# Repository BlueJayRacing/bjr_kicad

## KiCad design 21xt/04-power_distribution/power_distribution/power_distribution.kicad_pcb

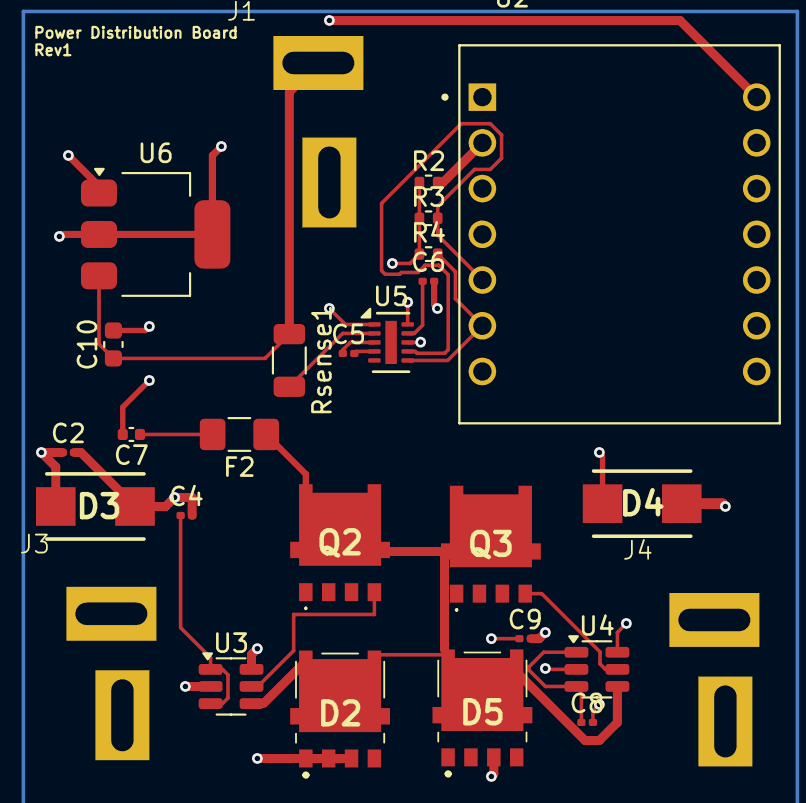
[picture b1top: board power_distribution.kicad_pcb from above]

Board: 4 copper layers, 27 parts (0 on the bottom side), 19 nets.

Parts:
C2, C4, C8, C9: 10 uF; C_0201_0603Metric
C5: 470 nF; C_0201_0603Metric
C6: 1 uF; C_0201_0603Metric
C7: 10uF; C_0402_1005Metric
C10: 100uF; C_0603_1608Metric
D2, D5: NRVB10100MFST1G; NRVTS10100EMFST1G
D3, D4: SMBJ33CA
F2: Fuse; Fuse_1206_3216Metric_Pad1.42x1.75mm_HandSolder
J1: Conn_01x02; Deans Connector Female
J3, J4: Conn_01x02; Deans Connector Male
Q2, Q3: NVMFWS2D1N08XT1G; NTMFWS1D5N08XT1G
R2, R3, R4: 2k; R_0402_1005Metric
Rsense1: 50 mOhms; R_1206_3216Metric
U2: XIAO-ESP32-C3-DIP; esp32 c6 xiao
U3, U4: LM74700; SOT-23-6
U5: LTC2959; DFN-10-1EP_2x3mm_P0.5mm_EP0.64x2.4mm
U6: TLV76150DCY; SOT-223-3_TabPin2

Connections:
3V3 ESP32: R2.1, R3.1, R4.1, U2.12 (VCC_3V3), U5.8 (GPIO)
5 LinReg: U2.14 (VBUS), U5.1 (V_{DD}), U6.2 (VO)
Battery1: C8.2, C9.2, D4.2, D5.1 (S_1), D5.2 (S_2), D5.3 (S_3), J4.1, U4.6 (ANODE)
Battery1_Supply: D2.5 (D_1), D2.6 (D_2), D2.7 (D_3), D2.8 (D_4), D2.9 (D_5), D5.5 (D_1), D5.6 (D_2), D5.7 (D_3), D5.8 (D_4), D5.9 (D_5), F2.1, Q2.5 (D_1), Q2.6 (D_2), Q2.7 (D_3), Q2.8 (D_4), Q2.9 (D_5), Q3.5 (D_1), Q3.6 (D_2), Q3.7 (D_3), Q3.8 (D_4), Q3.9 (D_5), U3.4 (CATHODE), U4.4 (CATHODE)
Battery2: C2.2, C4.2, D2.1 (S_1), D2.2 (S_2), D2.3 (S_3), D3.2, J3.1, U3.6 (ANODE)
GND: C2.1, C6.2, C7.2, C9.1, C10.2, D3.1, D4.1, J1.2, J3.2, J4.2, U2.13 (GND), U3.2 (GND), U4.2 (GND), U5.10 (GND), U6.1 (GND)
unnamed: C7.1, F2.2
unnamed: C10.1, J1.1, Rsense1.1, U6.3 (VI)
unnamed: Q2.4 (G), U3.5 (GATE)
unnamed: Q3.4 (G), U4.5 (GATE)
unnamed: R2.2, U2.2 (GPIO3/A1/D1)
unnamed: C4.1, U3.1 (VCAP), U3.3 (EN)
unnamed: C8.1, U4.1 (VCAP), U4.3 (EN)
unnamed: C5.2, U5.4 (CFN)
unnamed: C5.1, U5.3 (CFP)
unnamed: Rsense1.2, U5.2 (SENSEP)
unnamed: C6.1, U5.9 (V_{REG})
SCL: R4.2, U2.6 (GPIO7/D5/SCL), U5.6 (SCL)
SDA: R3.2, U2.5 (GPIO6/D4/SDA), U5.7 (SDA)

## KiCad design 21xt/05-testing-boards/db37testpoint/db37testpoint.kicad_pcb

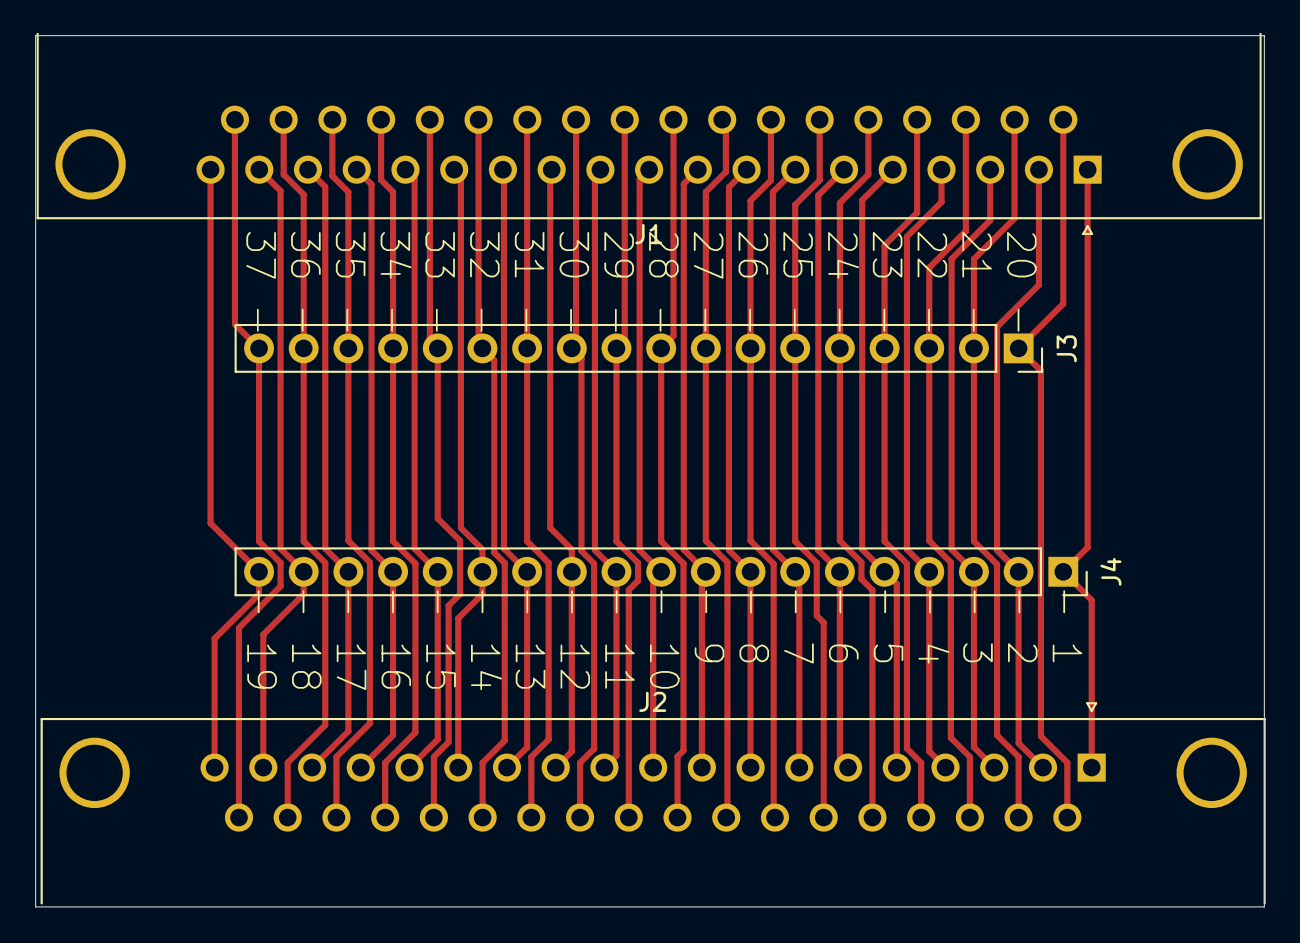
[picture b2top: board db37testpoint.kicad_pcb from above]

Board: 2 copper layers, 69.8 x 49.5 mm, 4 parts (0 on the bottom side), 37 nets.

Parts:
J1: DC37_Plug; DSUB-37_Male_Horizontal_P2.77x2.84mm_EdgePinOffset4.94mm_Ho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
J2: DC37_Receptacle; DSUB-37_Female_Horizontal_P2.77x2.84mm_EdgePinOffset4.94mm_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
J3: Conn_01x18_Pin; PinSocket_1x18_P2.54mm_Vertical
J4: Conn_01x19_Pin; PinSocket_1x19_P2.54mm_Vertical

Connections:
1: J1.1, J2.1, J4.1
2: J1.2, J2.2, J4.2
3: J1.3, J2.3, J4.3
4: J1.4, J2.4, J4.4
5: J1.5, J2.5, J4.5
6: J1.6, J2.6, J4.6
7: J1.7, J2.7, J4.7
8: J1.8, J2.8, J4.8
9: J1.9, J2.9, J4.9
10: J1.10, J2.10, J4.10
11: J1.11, J2.11, J4.11
12: J1.12, J2.12, J4.12
13: J1.13, J2.13, J4.13
14: J1.14, J2.14, J4.14
15: J1.15, J2.15, J4.15
16: J1.16, J2.16, J4.16
17: J1.17, J2.17, J4.17
18: J1.18, J2.18, J4.18
19: J1.19, J2.19, J4.19
20: J1.20, J2.20, J3.1
21: J1.21, J2.21, J3.2
22: J1.22, J2.22, J3.3
23: J1.23, J2.23, J3.4
24: J1.24, J2.24, J3.5
25: J1.25, J2.25, J3.6
26: J1.26, J2.26, J3.7
27: J1.27, J2.27, J3.8
28: J1.28, J2.28, J3.9
29: J1.29, J2.29, J3.10
30: J1.30, J2.30, J3.11
31: J1.31, J2.31, J3.12
32: J1.32, J2.32, J3.13
33: J1.33, J2.33, J3.14
34: J1.34, J2.34, J3.15
35: J1.35, J2.35, J3.16
36: J1.36, J2.36, J3.17
37: J1.37, J2.37, J3.18

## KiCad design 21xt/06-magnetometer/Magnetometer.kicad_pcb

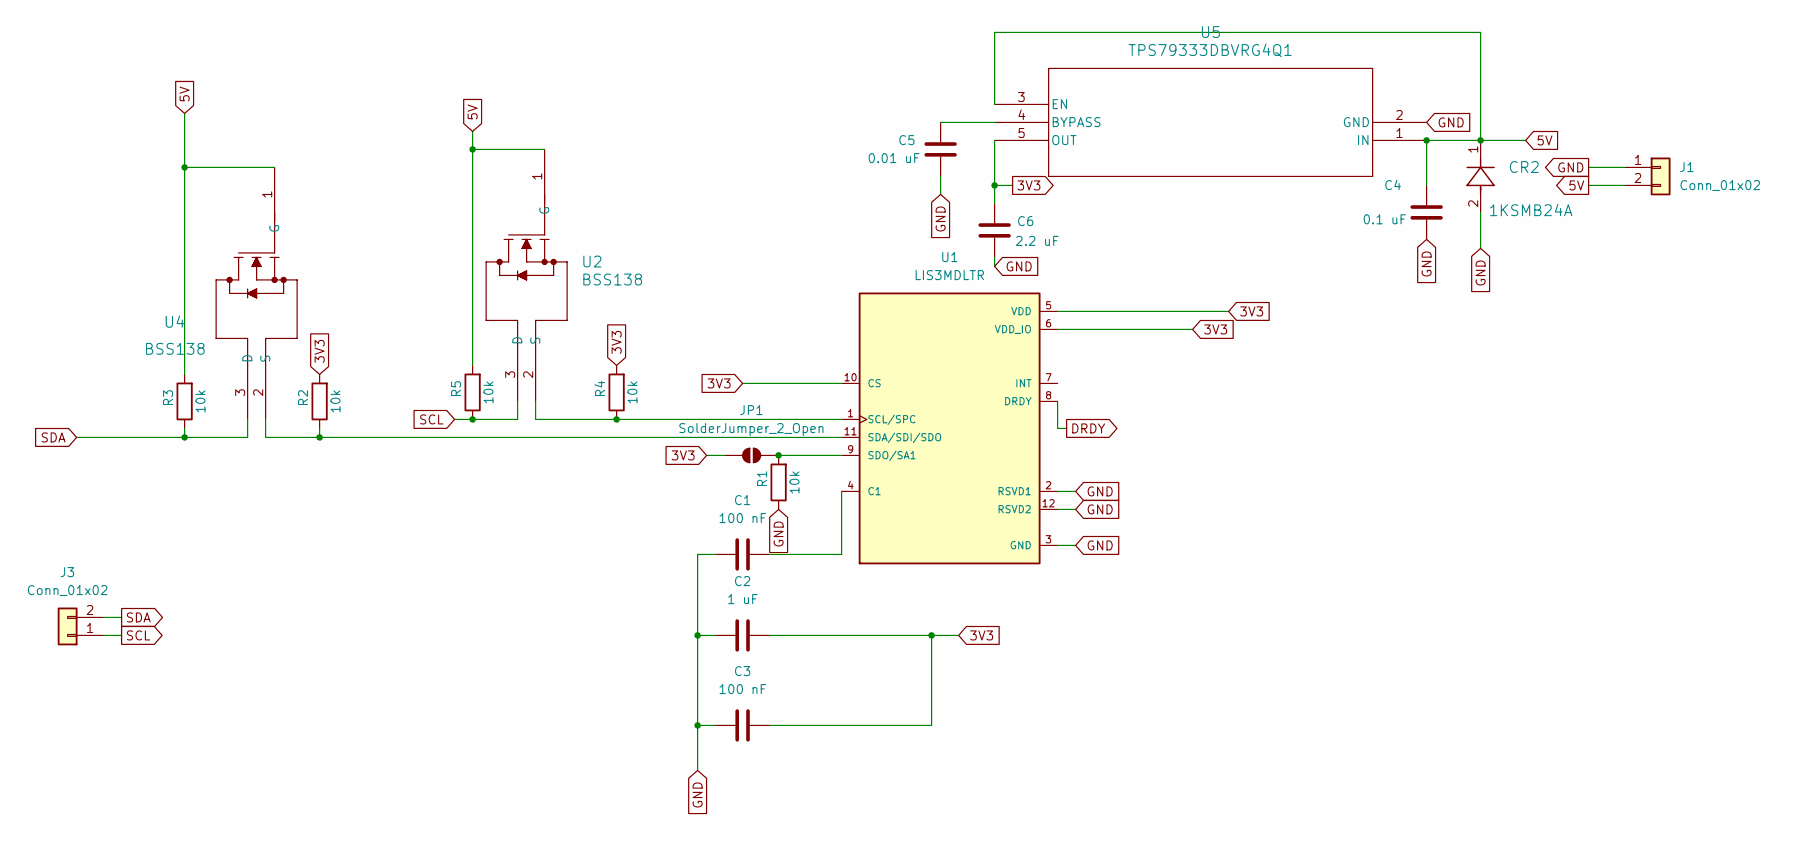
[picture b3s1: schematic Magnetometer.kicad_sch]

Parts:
C1, C3: 100 nF; C_0402_1005Metric
C2: 1 uF; C_0402_1005Metric
C4: 0.1 uF; C_0402_1005Metric
C5: 0.01 uF; C_0402_1005Metric
C6: 2.2 uF; C_0402_1005Metric
CR2: 1KSMB24A; 1KSMBSeries_LTF
J1, J3: Conn_01x02; Connector
JP1: SolderJumper_2_Open; SolderJumper
R1, R2, R3, R4, R5: 10k; R_0402_1005Metric
U1: LIS3MDLTR; PARTREV 6
U2, U4: BSS138
U5: TPS79333DBVRG4Q1; DBV5_TEX

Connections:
3V3: C2.2, C3.2, C6.1, JP1.1 (A), R2.2, R4.2, U1.5 (VDD), U1.6 (VDD_IO), U1.10 (CS), U5.5 (OUT)
5V: C4.1, CR2.1, J1.2, R3.2, R5.2, U2.1 (G), U4.1 (G), U5.1 (IN), U5.3 (EN)
DRDY: U1.8 (DRDY)
GND: C1.1, C2.1, C3.1, C4.2, C5.2, C6.2, CR2.2, J1.1, R1.1, U1.2 (RSVD1), U1.3 (GND), U1.12 (RSVD2), U5.2 (GND)
unnamed: JP1.2 (B), R1.2, U1.9 (SDO/SA1)
unnamed: C1.2, U1.4 (C1)
unnamed: R4.1, U1.1 (SCL/SPC), U2.2 (S)
unnamed: R2.1, U1.11 (SDA/SDI/SDO), U4.2 (S)
unnamed: C5.1, U5.4 (BYPASS)
SCL: J3.1, R5.1, U2.3 (D)
SDA: J3.2, R3.1, U4.3 (D)

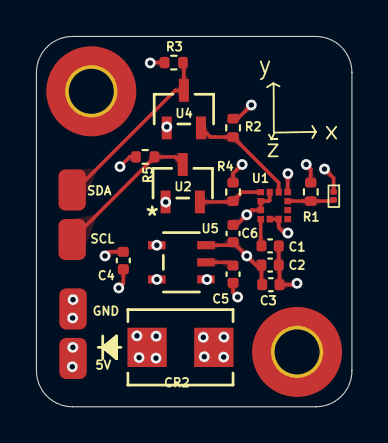
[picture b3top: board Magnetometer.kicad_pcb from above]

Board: 4 copper layers, 17.5 x 20.6 mm, 19 parts (0 on the bottom side), 10 nets.

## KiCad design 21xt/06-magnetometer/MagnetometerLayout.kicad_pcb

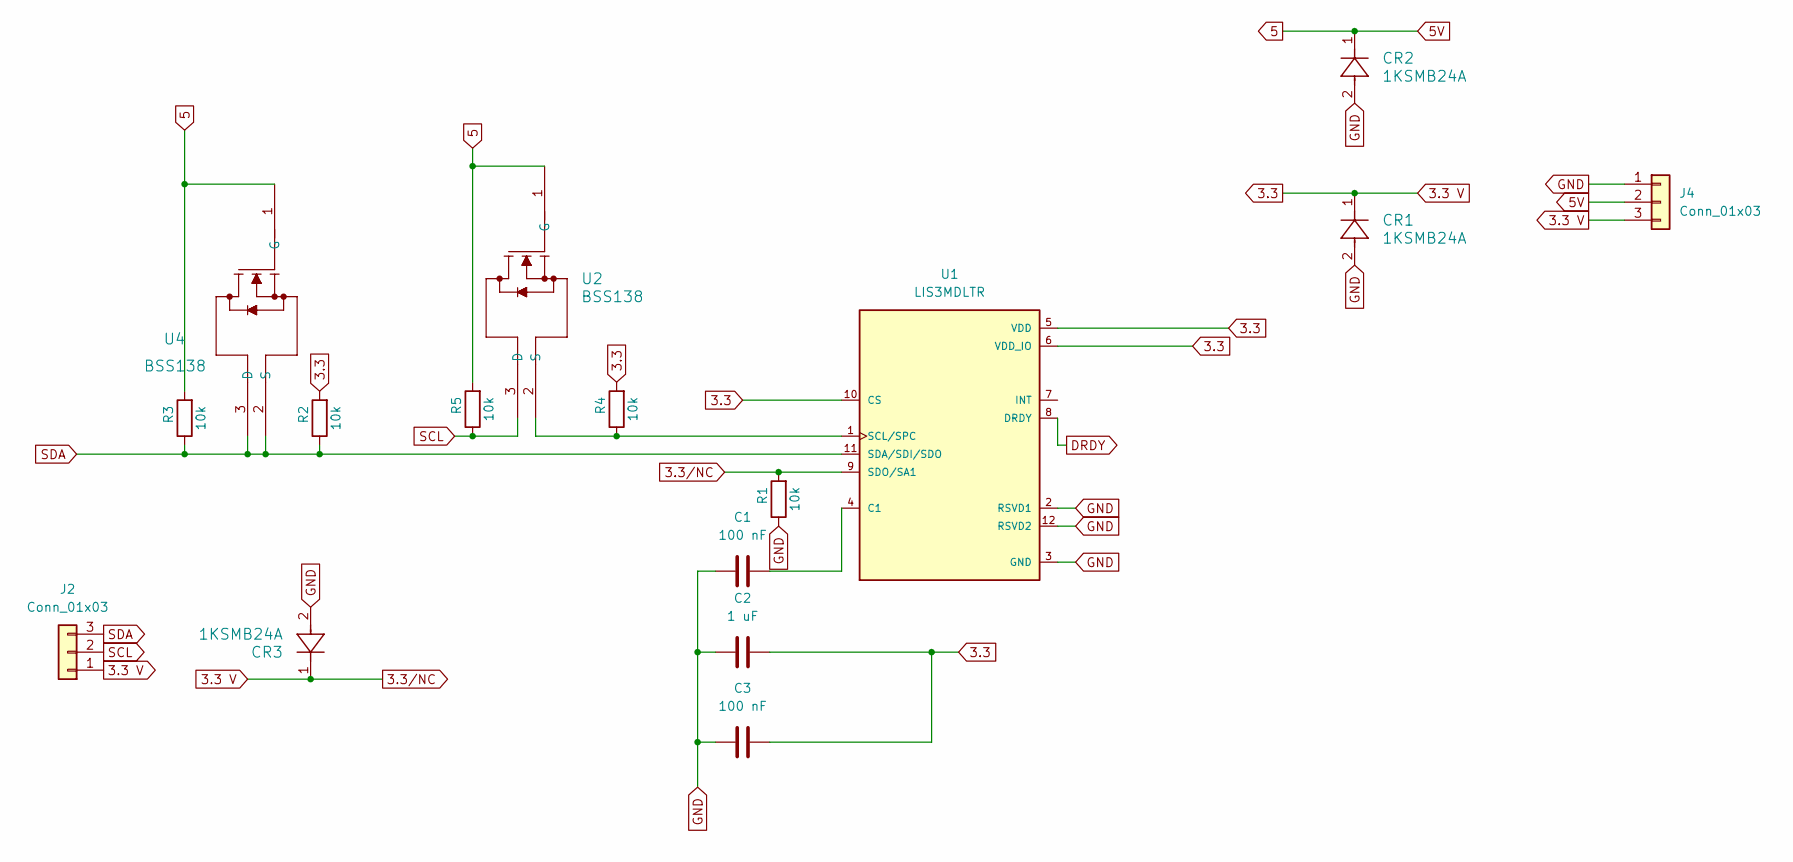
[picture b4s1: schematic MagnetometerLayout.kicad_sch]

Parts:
C1, C3: 100 nF; CP_Elec_3x5.3
C2: 1 uF; CP_Elec_3x5.3
CR1, CR2, CR3: 1KSMB24A
J2, J4: Conn_01x03; JST_EH_B3B-EH-A_1x03_P2.50mm_Vertical
R1, R2, R3, R4, R5: 10k; R_0201_0603Metric_Pad0.64x0.40mm_HandSolder
U1: LIS3MDLTR; XDCR_LIS3MDLTR; PARTREV 6
U2, U4: BSS138

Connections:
3.3: C2.2, C3.2, CR1.1, CR3.1, J2.1, J4.3, R1.2, R2.2, R4.2, U1.5 (VDD), U1.6 (VDD_IO), U1.9 (SDO/SA1), U1.10 (CS)
5: CR2.1, J4.2, R3.2, R5.2, U2.1 (G), U4.1 (G)
DRDY: U1.8 (DRDY)
GND: C1.1, C2.1, C3.1, CR1.2, CR2.2, CR3.2, J4.1, R1.1, U1.2 (RSVD1), U1.3 (GND), U1.12 (RSVD2)
unnamed: C1.2, U1.4 (C1)
unnamed: R4.1, U1.1 (SCL/SPC), U2.2 (S)
SCL: J2.2, R5.1, U2.3 (D)
SDA: J2.3, R2.1, R3.1, U1.11 (SDA/SDI/SDO), U4.2 (S), U4.3 (D)

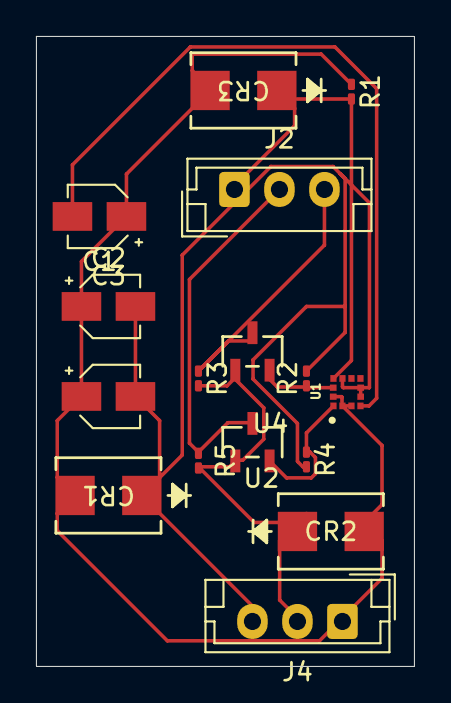
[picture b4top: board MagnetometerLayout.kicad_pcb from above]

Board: 2 copper layers, 21.0 x 35.0 mm, 16 parts (0 on the bottom side), 7 nets.

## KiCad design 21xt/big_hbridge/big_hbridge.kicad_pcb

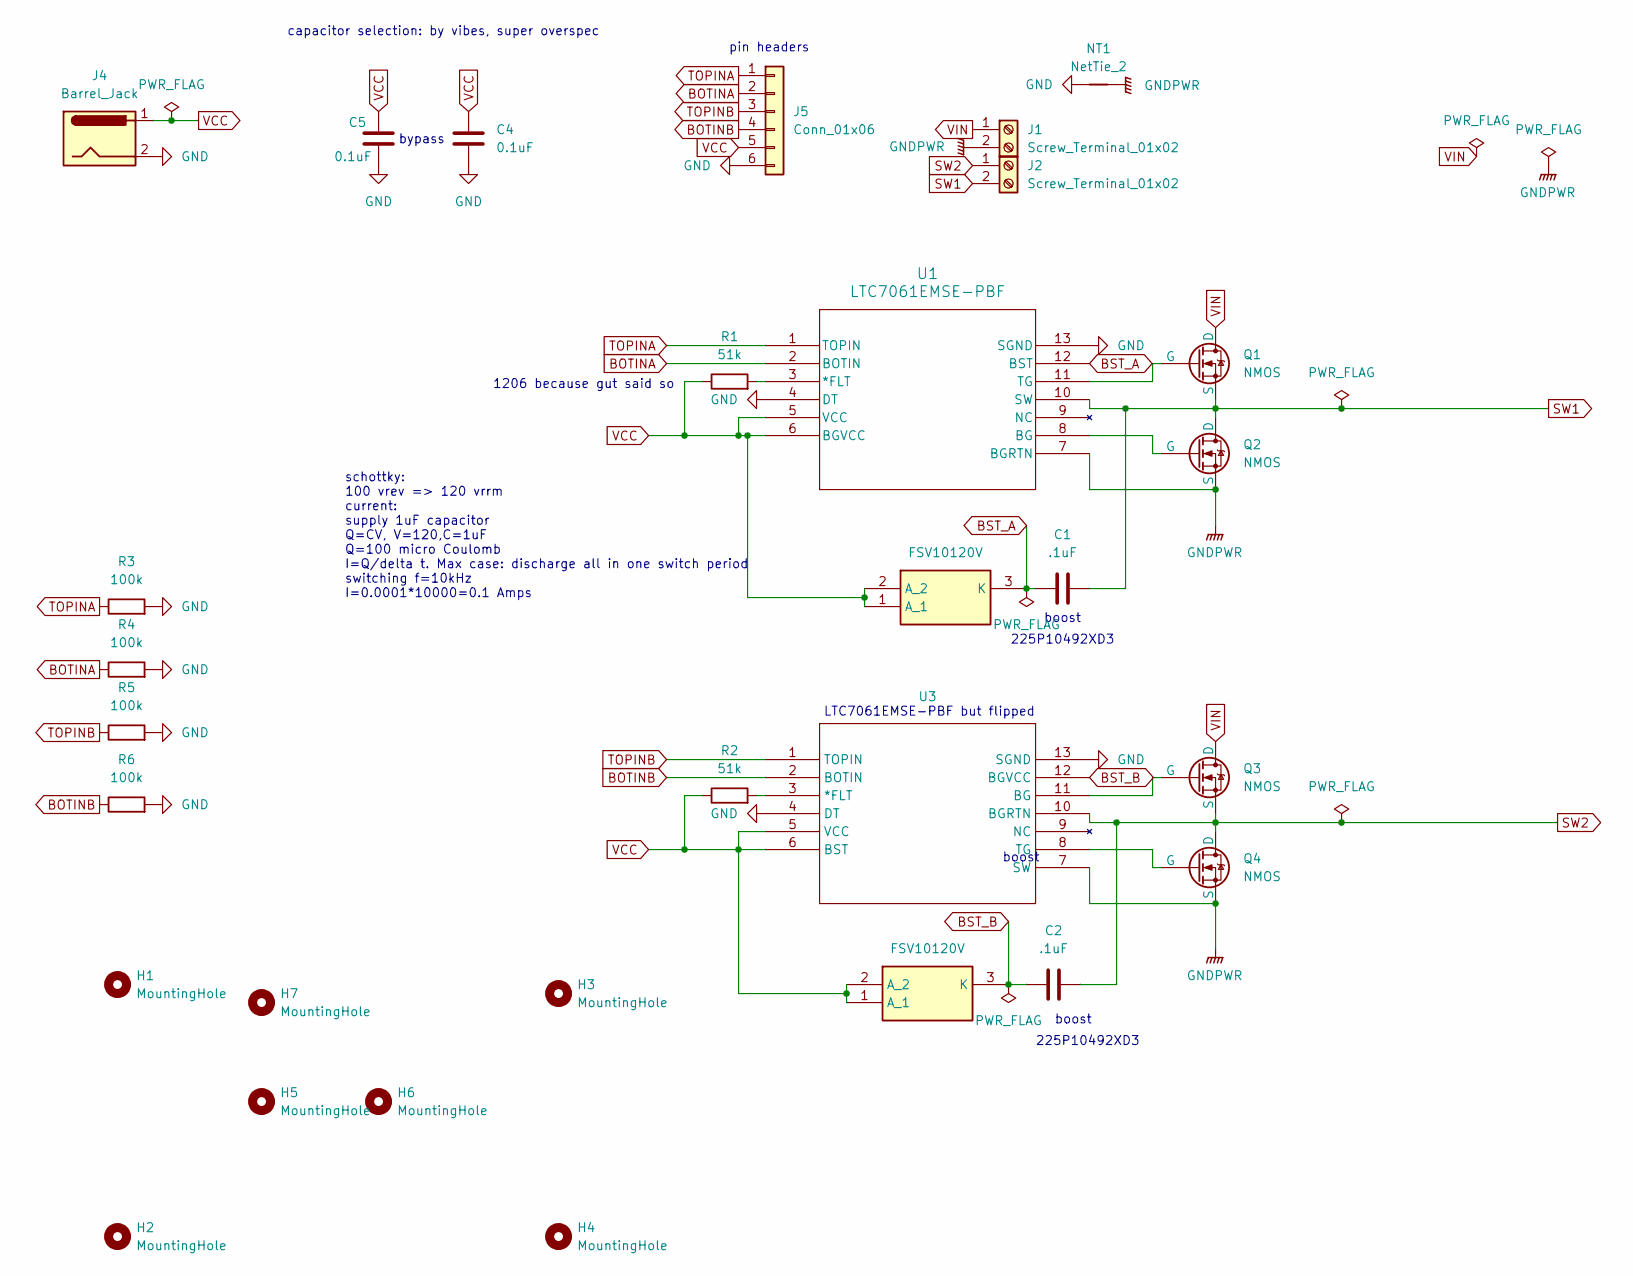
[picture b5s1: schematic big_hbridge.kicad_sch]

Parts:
C1, C2: .1uF; C_Disc_D7.5mm_W5.0mm_P10.00mm
C4, C5: 0.1uF; C_1206_3216Metric
D1, D3: FSV10120V; Mouser Part Number 512-FSV10120V
H1, H2, H3, H4, H5, H6, H7: MountingHole; MountingHole_3mm_Pad
J1, J2: Screw_Terminal_01x02; CONN_4DB-P108-02_TEC
J4: Barrel_Jack; BarrelJack_Horizontal
J5: Conn_01x06; PinHeader_1x06_P2.54mm_Vertical
NT1: NetTie_2; NetTie-2_THT_Pad1.0mm
Q1, Q2, Q3, Q4: NMOS; TO254P1524X483-3N
R1, R2: 51k; R_1206_3216Metric
R3, R4, R5: 100k; R_0402_1005Metric
R6: 100k; LED_0402_1005Metric
U1: LTC7061EMSE-PBF; MSOP12_MSE_ADI-M
U3: MSOP12_MSE_ADI-M

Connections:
BOTINA: J5.2, R4.1, U1.2 (BOTIN)
BOTINB: J5.4, R6.1, U3.2 (BOTIN)
BST_A: C1.1, D3.3 (K), U1.12 (BST)
BST_B: C2.1, D1.3 (K), U3.12 (BGVCC)
GND: C4.1, C5.1, J4.2, J5.6, NT1.1, R3.2, R4.2, R5.2, R6.2, U1.4 (DT), U1.13 (SGND), U3.4 (DT), U3.13 (SGND)
GNDPWR: J1.2, NT1.2, Q2.3 (S), Q4.3 (S), U1.7 (BGRTN), U3.7 (SW)
unnamed: Q1.2 (G), U1.11 (TG)
unnamed: Q2.2 (G), U1.8 (BG)
unnamed: Q3.2 (G), U3.11 (BG)
unnamed: Q4.2 (G), U3.8 (TG)
unnamed: R1.2, U1.3 (*FLT)
unnamed: R2.2, U3.3 (*FLT)
SW1: C1.2, J2.2, Q1.3 (S), Q2.1 (D), U1.10 (SW)
SW2: C2.2, J2.1, Q3.3 (S), Q4.1 (D), U3.10 (BGRTN)
TOPINA: J5.1, R3.1, U1.1 (TOPIN)
TOPINB: J5.3, R5.1, U3.1 (TOPIN)
VCC: C4.2, C5.2, D1.1 (A_1), D1.2 (A_2), D3.1 (A_1), D3.2 (A_2), J4.1, J5.5, R1.1, R2.1, U1.5 (VCC), U1.6 (BGVCC), U3.5 (VCC), U3.6 (BST)
VIN: J1.1, Q1.1 (D), Q3.1 (D)

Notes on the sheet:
schottky: 100 vrev => 120 vrrm current: supply 1uF capacitor Q=CV, V=120,C=1uF Q=100 micro Coulomb I=Q/delta t. Max case: discharge all in one switch period switching f=10kHz I=0.0001*10000=0.1 Amps
225P10492XD3
boost
1206 because gut said so
pin headers
LTC7061EMSE-PBF but flipped
bypass
capacitor selection: by vibes, super overspec

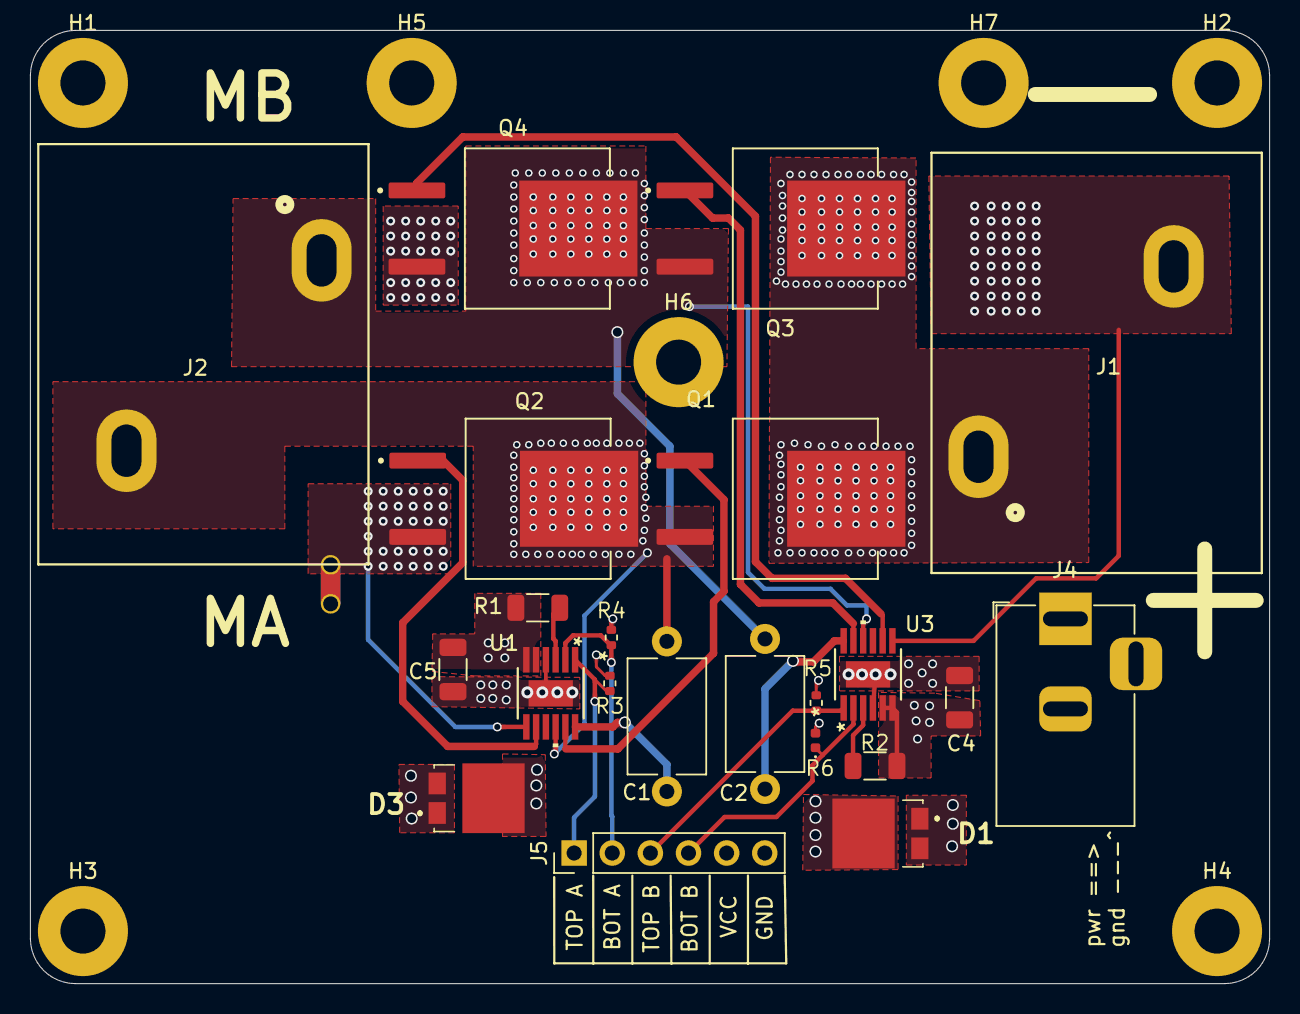
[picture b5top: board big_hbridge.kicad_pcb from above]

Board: 4 copper layers, 82.5 x 63.5 mm, 30 parts (0 on the bottom side), 18 nets.

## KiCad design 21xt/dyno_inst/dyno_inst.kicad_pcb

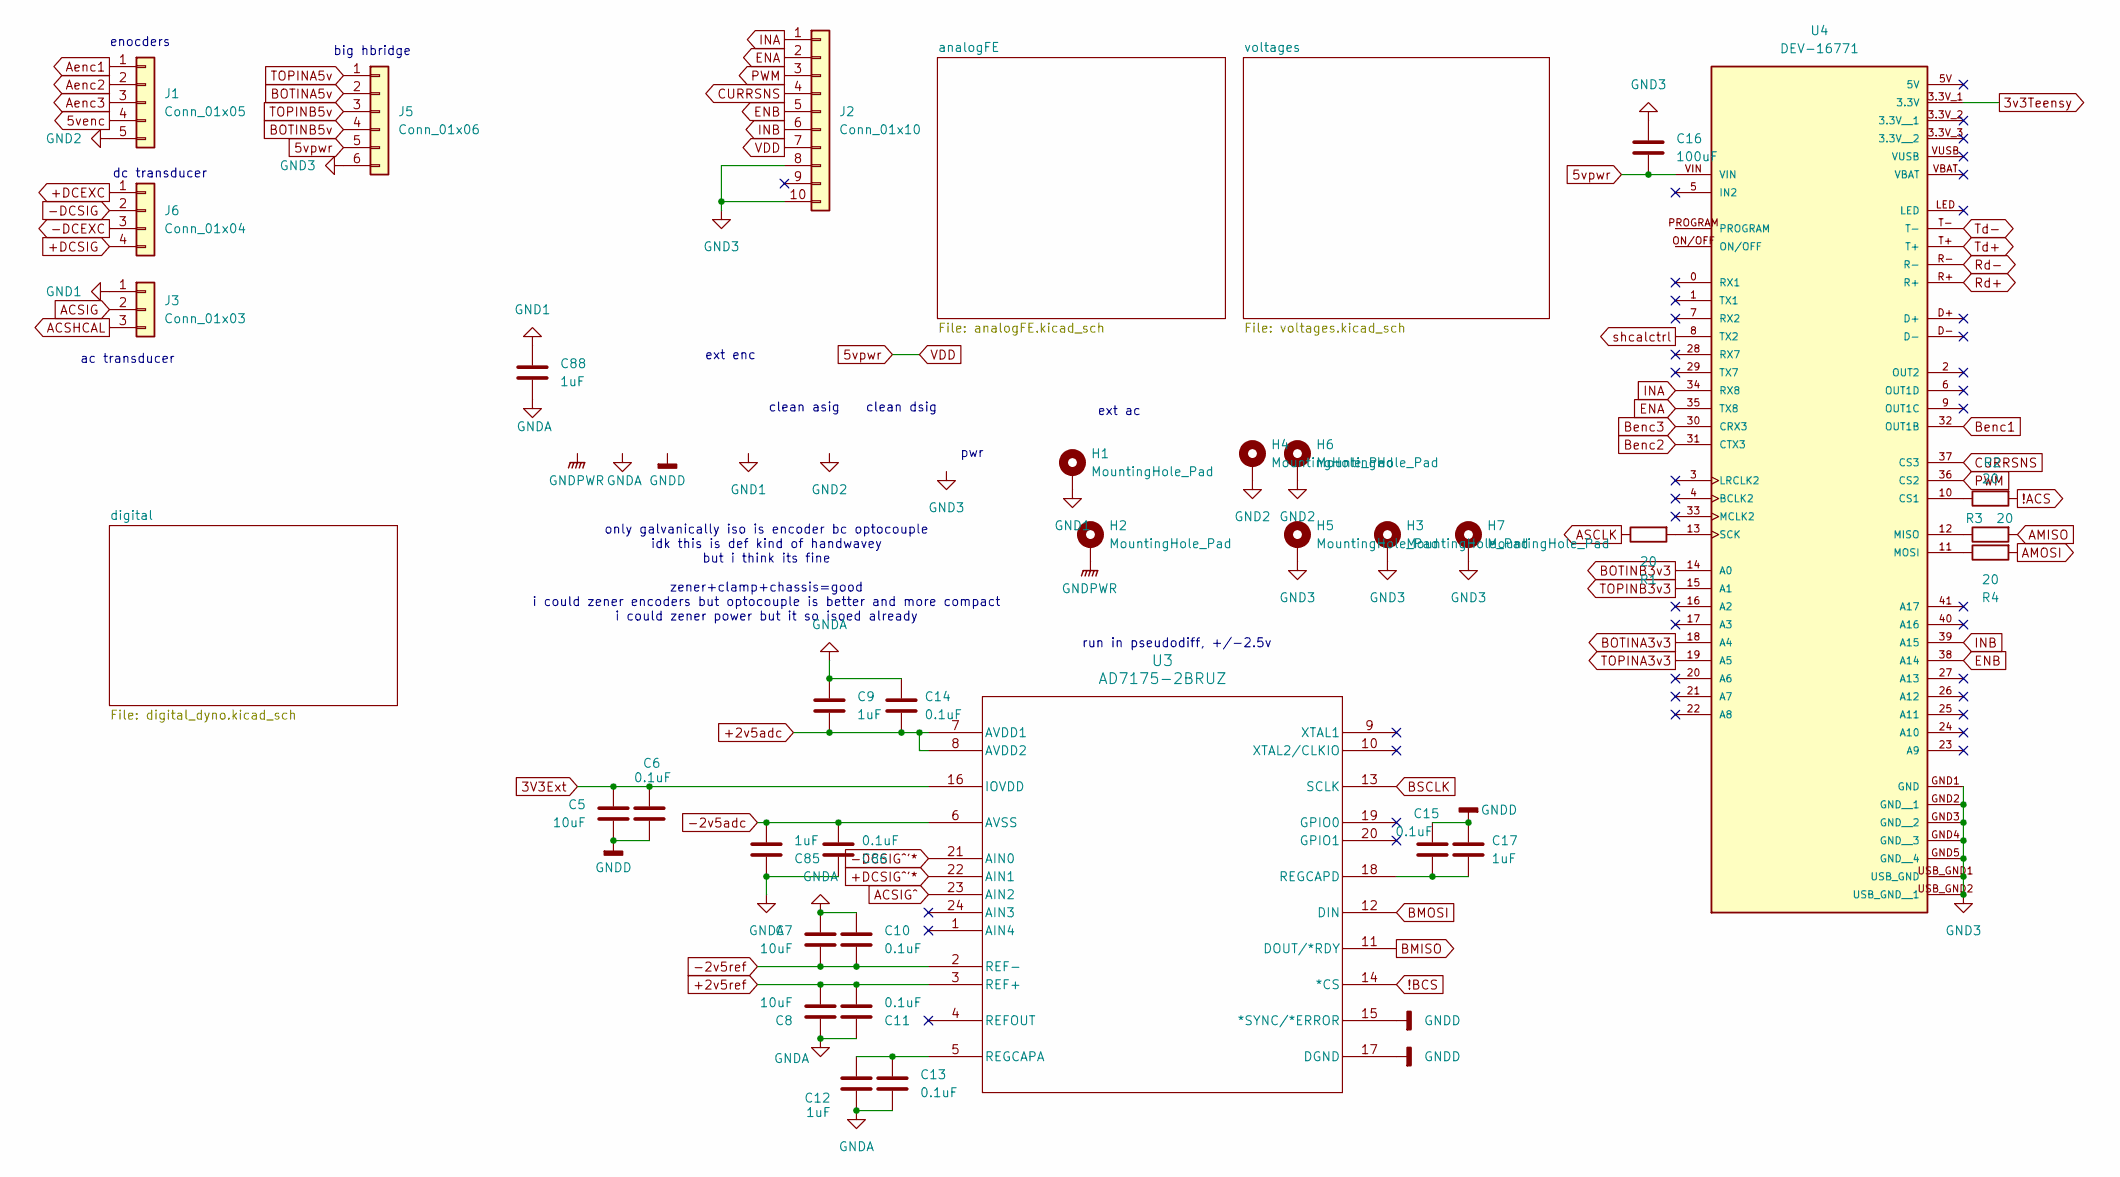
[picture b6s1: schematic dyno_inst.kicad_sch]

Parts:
C5, C7, C8: 10uF; C_0402_1005Metric
C6, C10, C11, C13, C14, C15, C86: 0.1uF; C_0402_1005Metric
C9, C12, C17, C85: 1uF; C_0402_1005Metric
C16: 100uF; C_0603_1608Metric
C88: 1uF; C_0603_1608Metric
H1, H2, H3, H4, H5, H6, H7: MountingHole_Pad; MountingHole_3mm_Pad
J1: Conn_01x05; PinHeader_1x05_P2.54mm_Vertical
J2: Conn_01x10; PinHeader_1x10_P2.54mm_Vertical
J3: Conn_01x03; CONN_T4041017041-000_TEC
J5: Conn_01x06; PinHeader_1x06_P2.54mm_Vertical
J6: Conn_01x04; CONN_T4041017041-000_TEC
R1, R2, R3, R4: 20; R_0402_1005Metric
U3: AD7175-2BRUZ; RU_24_ADI
U4: DEV-16771; MODULE_DEV-16771; PARTREV 4.1

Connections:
3V3Ext: C5.1, C6.1, U3.16 (IOVDD)
3v3Teensy: U4.3.3V_1 (3.3V); also elsewhere on the board
5venc: J1.4; also elsewhere on the board
5vpwr: C16.2, J2.7, J5.5, U4.VIN; also elsewhere on the board
!ACS: R2.2; also elsewhere on the board
!BCS: U3.14 (*CS); also elsewhere on the board
+2v5adc: C9.2, C14.2, U3.7 (AVDD1), U3.8 (AVDD2); also elsewhere on the board
+2v5ref: C8.2, C11.2, U3.3 (REF+); also elsewhere on the board
+5vexc: J6.1; also elsewhere on the board
+DCSIG: J6.4; also elsewhere on the board
+DCSIG^'*: U3.22 (AIN1); also elsewhere on the board
-2v5adc: C85.2, C86.2, U3.6 (AVSS); also elsewhere on the board
-2v5ref: C7.2, C10.2, U3.2 (REF-); also elsewhere on the board
-5vexc: J6.3; also elsewhere on the board
-DCSIG: J6.2; also elsewhere on the board
-DCSIG^'*: U3.21 (AIN0); also elsewhere on the board
ACSHCAL: J3.3; also elsewhere on the board
ACSIG: J3.2; also elsewhere on the board
ACSIG^: U3.23 (AIN2); also elsewhere on the board
AMISO: R3.2; also elsewhere on the board
AMOSI: R4.2; also elsewhere on the board
ASCLK: R1.1; also elsewhere on the board
Aenc1: J1.1; also elsewhere on the board
Aenc2: J1.2; also elsewhere on the board
Aenc3: J1.3; also elsewhere on the board
BMISO: U3.11 (DOUT/*RDY); also elsewhere on the board
BMOSI: U3.12 (DIN); also elsewhere on the board
BOTINA3v3: U4.18 (A4); also elsewhere on the board
BOTINA5v: J5.2; also elsewhere on the board
BOTINB3v3: U4.14 (A0); also elsewhere on the board
BOTINB5v: J5.4; also elsewhere on the board
BSCLK: U3.13 (SCLK); also elsewhere on the board
Benc1: U4.32 (OUT1B); also elsewhere on the board
Benc2: U4.31 (CTX3); also elsewhere on the board
Benc3: U4.30 (CRX3); also elsewhere on the board
CURRSNS: J2.4, U4.37 (CS3)
ENA: J2.2, U4.35 (TX8)
ENB: J2.5, U4.38 (A14)
GND1: C88.1, H1.1, J3.1; also elsewhere on the board
GND2: H4.1, H6.1, J1.5; also elsewhere on the board
GND3: C16.1, H3.1, H5.1, H7.1, J2.8, J2.10, J5.6, U4.GND1 (GND), U4.GND2 (GND__1), U4.GND3 (GND__2), U4.GND4 (GND__3), U4.GND5 (GND__4), U4.USB_GND1 (USB_GND), U4.USB_GND2 (USB_GND__1); also elsewhere on the board
GNDA: C7.1, C8.1, C9.1, C10.1, C11.1, C12.2, C13.2, C14.1, C85.1, C86.1, C88.2; also elsewhere on the board
GNDD: C5.2, C6.2, C15.1, C17.1, U3.15 (*SYNC/*ERROR), U3.17 (DGND); also elsewhere on the board
GNDPWR: H2.1; also elsewhere on the board
INA: J2.1, U4.34 (RX8)
INB: J2.6, U4.39 (A15)
unnamed: C12.1, C13.1, U3.5 (REGCAPA)
unnamed: C15.2, C17.2, U3.18 (REGCAPD)
unnamed: R2.1, U4.10 (CS1)
unnamed: R3.1, U4.12 (MISO)
unnamed: R4.1, U4.11 (MOSI)
unnamed: R1.2, U4.13 (SCK)
PWM: J2.3, U4.36 (CS2)
Rd+: U4.R+; also elsewhere on the board
Rd-: U4.R-; also elsewhere on the board
TOPINA3v3: U4.19 (A5); also elsewhere on the board
TOPINA5v: J5.1; also elsewhere on the board
TOPINB3v3: U4.15 (A1); also elsewhere on the board
TOPINB5v: J5.3; also elsewhere on the board
Td+: U4.T+; also elsewhere on the board
Td-: U4.T-; also elsewhere on the board
shcalctrl: U4.8 (TX2); also elsewhere on the board

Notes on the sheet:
dc transducer
clean dsig
big hbridge
pwr
ext enc
only galvanically iso is encoder bc optocouple idk this is def kind of handwavey but i think its fine zener+clamp+chassis=good i could zener encoders but optocouple is better and more compact i could zener power but it so isoed already
run in pseudodiff, +/-2.5v
ext ac
clean asig
enocders
ac transducer
